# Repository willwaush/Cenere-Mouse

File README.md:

# 🖱️ Cenere Mouse (Open Source Tri-Mode Connectivity)

---

## 🔎 Project Overview

This project is an **open-source tri-mode connectivity gaming mouse**, designed around the **Nordic nRF52840** SoC.  
It supports three connectivity modes:

- **USB HID**  
- **Bluetooth Low Energy (BLE)**  
- **Nordic 2.4 GHz Wireless protocol**  

### ✨ Key Features
- Custom **monopole 2.4 GHz PCB antenna** optimized for the nRF52840  
- **PixArt PAW3395 optical sensor** for high-precision tracking  
- **Battery charging circuit** to support Bluetooth and Wireless power  
- **DC/DC Supply** to achieve maximum efficiency, low energy consumption
- **Addressable RGB LEDs** to optionally enable some aestethic glowing effect
- Fully open-source hardware and firmware*

---

## 📐 PCB Layer Previews

The design is a **4-layer PCB**, manufactured by **JLCPCB**, chosen for their reliable stackup and cost-effective prototyping services.  

---

## 🏗️ PCB Stackup (JLCPCB)

The board will be fabricated at **JLCPCB** with the following stackup:

- **Top Layer (Copper, 35 µm)** – signal + components  
- **Prepreg (0.2104 mm, Dk ≈ 4.4)** – dielectric (7628*1) 
- **Mid Layer 1 (Copper, 152 µm)** – ground/pwr
- **Core (1.065 mm, Dk ≈ 4.6)** – dielectric (FR4)
- **Mid Layer 2 (Copper, 152 µm)** – ground/pwr
- **Prepreg (0.2104 mm, Dk ≈ 4.4)** – dielectric (7628*1) 
- **Bottom Layer (Copper, 35 µm)** – signal + components

This configuration provides an easy to work with controlled impedance environment for the **high speed signals** as well as the **RF Section**.

---

## 🚀 Goals

- Provide a **fully open-source reference design** for hobbyists, makers, and researchers  
- Explore advanced **antenna design** on low-cost PCB fabrication  
- Enable experimentation with **custom gaming peripherals**  

---

## 📂 Repository Structure

/Kicad Files        → KiCad design files
/Electronics Docs   → Documentation, layer renders, diagrams

Work in progress..

---

## 📜 License

This project uses a **dual-license** model:

- **Software (Code)** → [GNU GPL v3.0](LICENSES/GPL-3.0.txt) with a **Non-Commercial Use Exception**  
  - You may use, modify, and redistribute the source code for **personal, educational, or research** purposes.  
  - **Commercial use is prohibited** without prior written permission.  
  - Attribution is required.

- **Hardware (Schematics, PCB Layouts, Documentation)** → [CC BY-NC 4.0](LICENSES/CC-BY-NC-4.0.txt)  
  - You may copy, redistribute, remix, and adapt the hardware files.  
  - **Commercial use is prohibited.**  
  - Attribution is required.

### Attribution Requirement

If you use this project (code or hardware) in your own work, you must credit:

**© [Your Name or Handle] – [Year]**  
Repo: [GitHub Repository URL]

Example attribution:  
> “Based on the open-source design/code by [Your Name], available at [GitHub Repo URL].”

### Commercial Use

For commercial licensing, please contact the author.

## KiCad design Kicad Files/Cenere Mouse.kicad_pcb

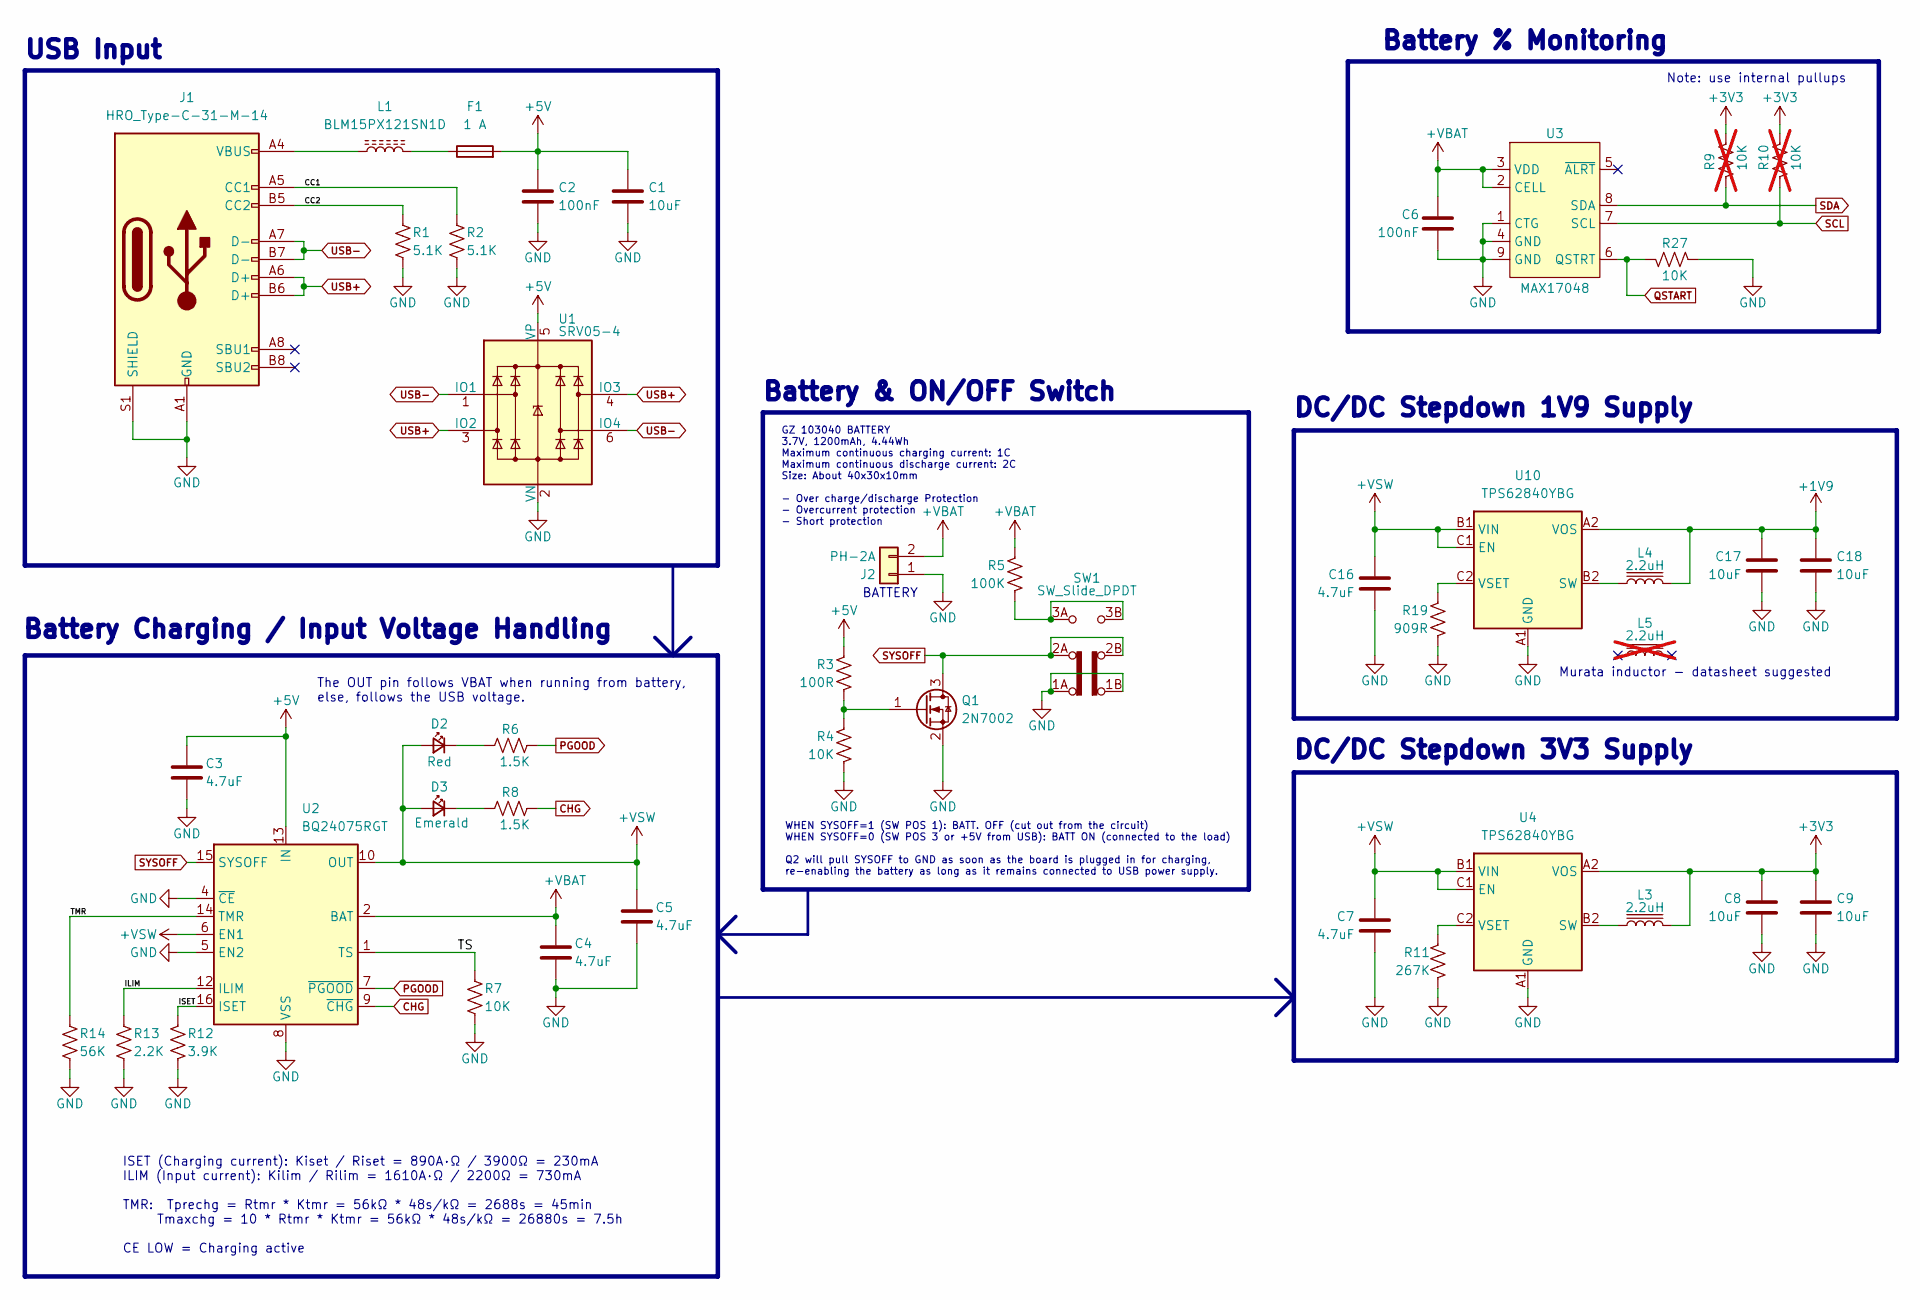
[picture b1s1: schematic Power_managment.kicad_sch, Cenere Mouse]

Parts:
C1, C9, C18: 10uF; C_0805_2012Metric; Part Number CL21B106KOQNNNE; JLCPCB PN C95841
C2: 100nF; C_0805_2012Metric; Part Number CC0805KRX7R9BB104; JLCPCB PN C49678
C3: 4.7uF; C_1206_3216Metric; Part Number 1206B475K500NT; JLCPCB PN C29823
C4, C5: 4.7uF; C_0805_2012Metric; Part Number CGA0805X7R475K350MT; JLCPCB PN C6119943
C6: 100nF; C_0402_1005Metric; Part Number CL05B104KB54PNC; JLCPCB PN C307331
C7, C16: 4.7uF; C_0402_1005Metric; Part Number CL05A475MP5NRNC; JLCPCB PN C23733
C8, C17: 10uF; C_0402_1005Metric; Part Number CL05A106MQ5NUNC; JLCPCB PN C15525
D2: Red; LED_0603_1608Metric; Part Number KT-0603R; JLCPCB PN C2286
D3: Emerald; LED_0603_1608Metric; Part Number APTD1608CGCK; JLCPCB PN C5121471
F1: 1 A; Fuse_0603_1608Metric; Part Number 0467001.NRHF; JLCPCB PN C151139
J1: HRO_Type-C-31-M-14; USB_C_Receptacle_HRO_TYPE-C-31-M-14; Part Number TYPE-C-31-M-14; JLCPCB PN C223907
J2: PH-2A; JST_PH_B2B-PH-K_1x02_P2.00mm_Vertical; Part Number PH-2A; JLCPCB PN C2319
L1: BLM15PX121SN1D; L_0402_1005Metric; Part Number BLM15PX121SN1D; JLCPCB PN C88970
L3, L4: 2.2uH; L_1008_2520Metric; Part Number FTC252012S2R2MBCA; JLCPCB PN C5832372
L5: 2.2uH; L_Murata_DFE201610P; Part Number DFE201612E-2R2M=P2; JLCPCB PN C337893; not fitted
Q1: 2N7002; SOT-23; Part Number 2N7002; JLCPCB PN C8545
R1, R2: 5.1K; R_0603_1608Metric; Part Number 0603WAF5101T5E; JLCPCB PN C23186
R3: 100R; R_0603_1608Metric; Part Number 0603WAF1000T5E; JLCPCB PN C22775
R4, R27: 10K; R_0603_1608Metric; Part Number 0603WAF1002T5E; JLCPCB PN C25804
R5: 100K; R_0603_1608Metric; Part Number 0603WAF1003T5E; JLCPCB PN C25803
R6, R8: 1.5K; R_0603_1608Metric; Part Number 0603WAF1501T5E; JLCPCB PN C22843
R7: 10K; R_0805_2012Metric; Part Number 0805W8F1002T5E; JLCPCB PN C17414
R9, R10: 10K; R_0603_1608Metric; Part Number 0603WAF1002T5E; JLCPCB PN C25804; not fitted
R11: 267K; R_0402_1005Metric; Part Number FRC0402F2673TS; JLCPCB PN C2998050
R12: 3.9K; R_0603_1608Metric; Part Number 0603WAF3901T5E; JLCPCB PN C23018
R13: 2.2K; R_0402_1005Metric; Part Number 0402WGF2201TCE; JLCPCB PN C25879
R14: 56K; R_0402_1005Metric; Part Number 0402WGF5602TCE; JLCPCB PN C25796
R19: 909R; R_0603_1608Metric; Part Number RC0603DR-07909RL; JLCPCB PN C471842
SW1: SW_Slide_DPDT; SLIDE SMD DPDT
U1: SRV05-4; SOT-23-6; Part Number SRV05-4; JLCPCB PN C2836319
U2: BQ24075RGT; VQFN-16-1EP_3x3mm_P0.5mm_EP1.6x1.6mm_ThermalVias; Part Number BQ24075RGTR; JLCPCB PN C15464
U3: MAX17048; TDFN-8-EP_2x2mm_EP_0.8x1.38mm; Part Number MAX17048G+T10; JLCPCB PN C2682616
U4, U10: TPS62840YBG; Texas_DSBGA-6_0.76x1.16mm_Layout2x3_P0.4mm; Part Number TPS62840YBGR; JLCPCB PN C2071139

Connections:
+1V9: C17.1, C18.1, L4.2, U10.A2 (VOS); also elsewhere on the board
+3V3: C8.1, C9.1, L3.2, R9.2, R10.2, U4.A2 (VOS); also elsewhere on the board
+5V: C1.1, C2.1, C3.1, F1.2, R3.1, U1.5 (VP), U2.13 (IN); also elsewhere on the board
+VBAT: C4.1, C6.1, J2.2, R5.1, U2.2 (BAT), U2.3 (BAT), U3.2 (CELL), U3.3 (VDD)
+VSW: C5.1, C7.1, C16.1, D2.2 (A), D3.2 (A), U2.6 (EN1), U2.10 (OUT), U2.11 (OUT), U4.B1 (VIN), U4.C1 (EN), U10.B1 (VIN), U10.C1 (EN); also elsewhere on the board
/Power_managment/CC1: J1.A5 (CC1), R2.1
/Power_managment/CC2: J1.B5 (CC2), R1.1
/Power_managment/ILIM: R13.1, U2.12 (ILIM)
/Power_managment/ISET: R12.1, U2.16 (ISET)
/Power_managment/TMR: R14.1, U2.14 (TMR)
/Power_managment/TS: R7.1, U2.1 (TS)
CHG: R8.2, U2.9 (~CHG)
GND: C1.2, C2.2, C3.2, C4.2, C5.2, C6.2, C7.2, C8.2, C9.2, C16.2, C17.2, C18.2, J1.A1 (GND), J1.A12 (GND), J1.B1 (GND), J1.B12 (GND), J1.S1 (SHIELD), J2.1, Q1.2 (S), R1.2, R2.2, R4.2, R7.2, R11.2, R12.2, R13.2, R14.2, R19.2, R27.2, SW1.1A (NC), SW1.1B (NC), U1.2 (VN), U2.4 (~CE), U2.5 (EN2), U2.8 (VSS), U2.17 (VSS), U3.1 (CTG), U3.4 (GND), U3.9 (GND), U4.A1 (GND), U10.A1 (GND); also elsewhere on the board
unnamed: D2.1 (K), R6.1
unnamed: D3.1 (K), R8.1
unnamed: F1.1, L1.2
unnamed: J1.A4 (VBUS), J1.A9 (VBUS), J1.B4 (VBUS), J1.B9 (VBUS), L1.1
unnamed: Q1.1 (G), R3.2, R4.1
unnamed: R5.2, SW1.3A (NO), SW1.3B (NO)
unnamed: L3.1, U4.B2 (SW)
unnamed: R11.1, U4.C2 (VSET)
unnamed: L4.1, U10.B2 (SW)
unnamed: R19.1, U10.C2 (VSET)
PGOOD: R6.2, U2.7 (~PGOOD)
QSTART: R27.1, U3.6 (QSTRT); also elsewhere on the board
SCL: R10.1, U3.7 (SCL); also elsewhere on the board
SDA: R9.1, U3.8 (SDA); also elsewhere on the board
SYSOFF: Q1.3 (D), SW1.2A (COM), SW1.2B (COM), U2.15 (SYSOFF)
USB+: J1.A6 (D+), J1.B6 (D+), U1.3 (IO2), U1.4 (IO3); also elsewhere on the board
USB-: J1.A7 (D-), J1.B7 (D-), U1.1 (IO1), U1.6 (IO4); also elsewhere on the board

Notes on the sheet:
Note: use internal pullups
The OUT pin follows VBAT when running from battery, else, follows the USB voltage.
BATTERY
USB Input
GZ 103040 BATTERY 3.7V, 1200mAh, 4.44Wh Maximum continuous charging current: 1C Maximum continuous discharge current: 2C Size: About 40x30x10mm - Over charge/discharge Protection - Overcurrent protection - Short protection
DC/DC Stepdown 1V9 Supply
WHEN SYSOFF=1 (SW POS 1): BATT. OFF (cut out from the circuit) WHEN SYSOFF=0 (SW POS 3 or +5V from USB): BATT ON (connected to the load) Q2 will pull SYSOFF to GND as soon as the board is plugged in for charging, re-enabling the battery as long as it remains connected to USB power supply.
Battery % Monitoring
Murata inductor - datasheet suggested
Battery Charging / Input Voltage Handling
DC/DC Stepdown 3V3 Supply
Battery & ON/OFF Switch
ISET (Charging current): Kiset / Riset = 890A·Ω / 3900Ω = 230mA ILIM (Input current): Kilim / Rilim = 1610A·Ω / 2200Ω = 730mA TMR: Tprechg = Rtmr * Ktmr = 56kΩ * 48s/kΩ = 2688s = 45min Tmaxchg = 10 * Rtmr * Ktmr = 56kΩ * 48s/kΩ = 26880s = 7.5h CE LOW = Charging active

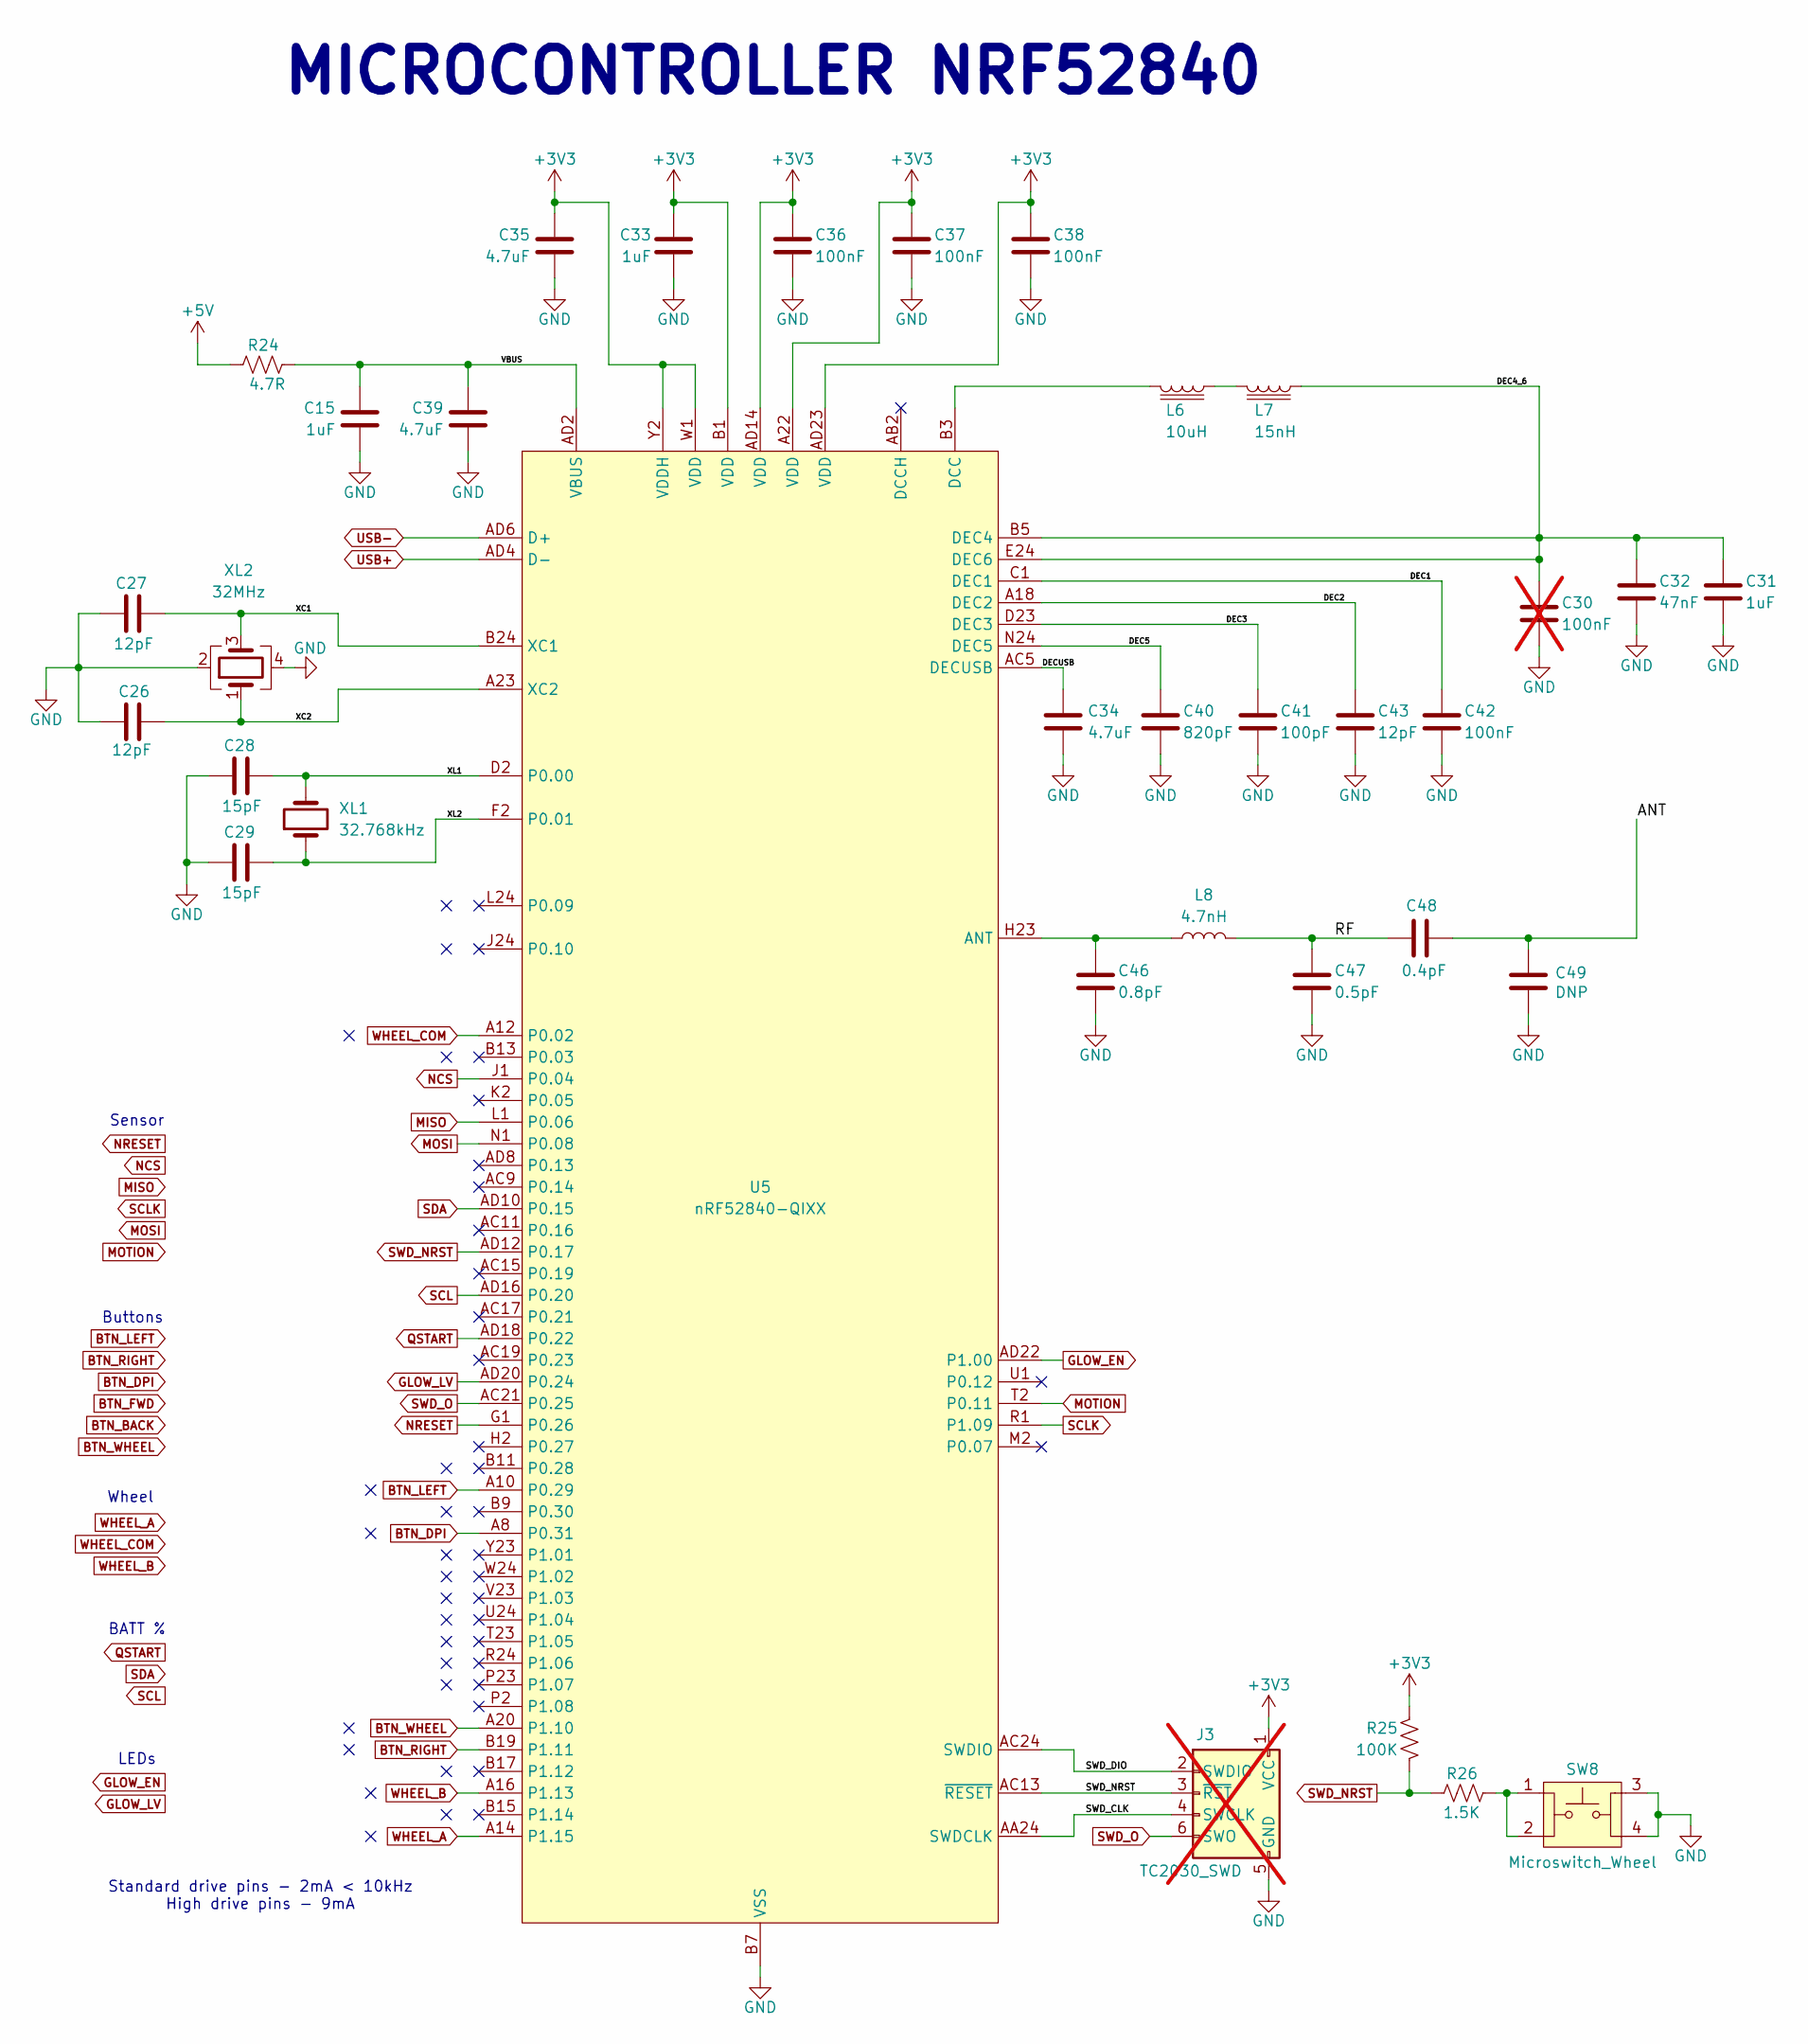
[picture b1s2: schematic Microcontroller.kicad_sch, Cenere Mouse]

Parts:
C15, C31, C33: 1uF; C_0402_1005Metric; Part Number CL05A105KA5NQNC; JLCPCB PN C52923
C26, C27, C43: 12pF; C_0402_1005Metric; Part Number 0402CG120J500NT; JLCPCB PN C1547
C28, C29: 15pF; C_0402_1005Metric; Part Number 0402CG150J500NT; JLCPCB PN C1548
C30: 100nF; C_0201_0603Metric; not fitted
C32: 47nF; C_0402_1005Metric; Part Number CC0402KRX7R9BB473; JLCPCB PN C272875
C34, C35, C39: 4.7uF; C_0402_1005Metric; Part Number CL05A475MP5NRNC; JLCPCB PN C23733
C36, C37, C38, C42: 100nF; C_0402_1005Metric; Part Number CL05B104KB54PNC; JLCPCB PN C307331
C40: 820pF; C_0402_1005Metric; Part Number CL05C821JB5NNNC; JLCPCB PN C307452
C41: 100pF; C_0402_1005Metric; Part Number 0402CG101J500NT; JLCPCB PN C1546
C46: 0.8pF; C_0402_1005Metric; Part Number GJM1555C1HR80WB01D; JLCPCB PN C88902
C47: 0.5pF; C_0402_1005Metric; Part Number GCM1555C1HR50WA16D; JLCPCB PN C2912277
C48: 0.4pF; Z0201 RF Antenna Path; Part Number GRM0335C1ER40WA01D; JLCPCB PN C710805
C49: DNP; Z0201 RF Antenna Path
J3: TC2030_SWD; CON_TC2030_outlined; not fitted
L6: 10uH; L_0603_1608Metric; Part Number LBMF1608T100M; JLCPCB PN C86752
L7: 15nH; L_0402_1005Metric; Part Number LQW15AN15NG80D; JLCPCB PN C668460
L8: 4.7nH; L_0402_1005Metric; Part Number LQG15HS4N7S02D; JLCPCB PN C86065
R24: 4.7R; R_0603_1608Metric; Part Number 0603WAF470KT5E; JLCPCB PN C23164
R25: 100K; R_0402_1005Metric; Part Number 0402WGF1003TCE; JLCPCB PN C25741
R26: 1.5K; R_0402_1005Metric; Part Number 0402WGF1501TCE; JLCPCB PN C25867
SW8: Microswitch_Wheel; KEY-SMD_4P-L4.2-W3.2-P2.20-LS4.6; Part Number SKRPACE010; JLCPCB PN C139797
U5: nRF52840-QIXX; Nordic_AQFN-73-1EP_7x7mm_P0.5mm; Part Number NRF52840-QIAA-R; JLCPCB PN C190794
XL1: 32.768kHz; Crystal_SMD_2012-2Pin_2.0x1.2mm; Part Number XKHEL89CGI-112YLC-32.768K; JLCPCB PN C7500573
XL2: 32MHz; Crystal_SMD_2016-4Pin_2.0x1.6mm; Part Number XL7EL89CKI-111YLC-32M; JLCPCB PN C2965582

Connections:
+3V3: C33.1, C35.1, C36.1, C37.1, C38.1, J3.1 (VCC), R25.1, U5.A22 (VDD), U5.AD14 (VDD), U5.AD23 (VDD), U5.B1 (VDD), U5.W1 (VDD), U5.Y2 (VDDH); also elsewhere on the board
+5V: R24.1; also elsewhere on the board
/Microcontroller/ANT: C48.2, C49.2
/Microcontroller/DEC1: C42.1, U5.C1 (DEC1)
/Microcontroller/DEC2: C43.2, U5.A18 (DEC2)
/Microcontroller/DEC3: C41.1, U5.D23 (DEC3)
/Microcontroller/DEC4_6: C30.1, C31.1, C32.1, L7.1, U5.B5 (DEC4), U5.E24 (DEC6)
/Microcontroller/DEC5: C40.1, U5.N24 (DEC5)
/Microcontroller/DECUSB: C34.1, U5.AC5 (DECUSB)
/Microcontroller/RF: C47.1, C48.1, L8.2
/Microcontroller/SWD_CLK: J3.4 (SWCLK), U5.AA24 (SWDCLK)
/Microcontroller/SWD_DIO: J3.2 (SWDIO), U5.AC24 (SWDIO)
/Microcontroller/VBUS: C15.1, C39.1, R24.2, U5.AD2 (VBUS)
/Microcontroller/XC1: C27.2, U5.B24 (XC1), XL2.3
/Microcontroller/XC2: C26.1, U5.A23 (XC2), XL2.1
/Microcontroller/XL1: C28.2, U5.D2 (P0.00), XL1.2
/Microcontroller/XL2: C29.2, U5.F2 (P0.01), XL1.1
BTN_DPI: U5.A8 (P0.31); also elsewhere on the board
BTN_LEFT: U5.A10 (P0.29); also elsewhere on the board
BTN_RIGHT: U5.B19 (P1.11); also elsewhere on the board
BTN_WHEEL: U5.A20 (P1.10); also elsewhere on the board
GLOW_EN: U5.AD22 (P1.00); also elsewhere on the board
GLOW_LV: U5.AD20 (P0.24); also elsewhere on the board
GND: C15.2, C26.2, C27.1, C28.1, C29.1, C30.2, C31.2, C32.2, C33.2, C34.2, C35.2, C36.2, C37.2, C38.2, C39.2, C40.2, C41.2, C42.2, C43.1, C46.2, C47.2, C49.1, J3.5 (GND), SW8.3, SW8.4, U5.B7 (VSS), U5.EP (VSS), U5.F23 (VSS_PA), XL2.2, XL2.4; also elsewhere on the board
MISO: U5.L1 (P0.06); also elsewhere on the board
MOSI: U5.N1 (P0.08); also elsewhere on the board
MOTION: U5.T2 (P0.11); also elsewhere on the board
NCS: U5.J1 (P0.04); also elsewhere on the board
NRESET: U5.G1 (P0.26); also elsewhere on the board
unnamed: L6.1, L7.2
unnamed: R26.2, SW8.1, SW8.2
unnamed: C46.1, L8.1, U5.H23 (ANT)
unnamed: L6.2, U5.B3 (DCC)
QSTART: U5.AD18 (P0.22); also elsewhere on the board
SCL: U5.AD16 (P0.20); also elsewhere on the board
SCLK: U5.R1 (P1.09); also elsewhere on the board
SDA: U5.AD10 (P0.15); also elsewhere on the board
SWD_NRST: J3.3 (~RST), R25.2, R26.1, U5.AC13 (~RESET), U5.AD12 (P0.17)
SWD_O: J3.6 (SWO), U5.AC21 (P0.25)
USB+: U5.AD4 (D-); also elsewhere on the board
USB-: U5.AD6 (D+); also elsewhere on the board
WHEEL_A: U5.A14 (P1.15); also elsewhere on the board
WHEEL_B: U5.A16 (P1.13); also elsewhere on the board
WHEEL_COM: U5.A12 (P0.02); also elsewhere on the board

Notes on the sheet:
Standard drive pins - 2mA < 10kHz High drive pins - 9mA
BATT %
Buttons
MICROCONTROLLER NRF52840
Sensor
Wheel
LEDs

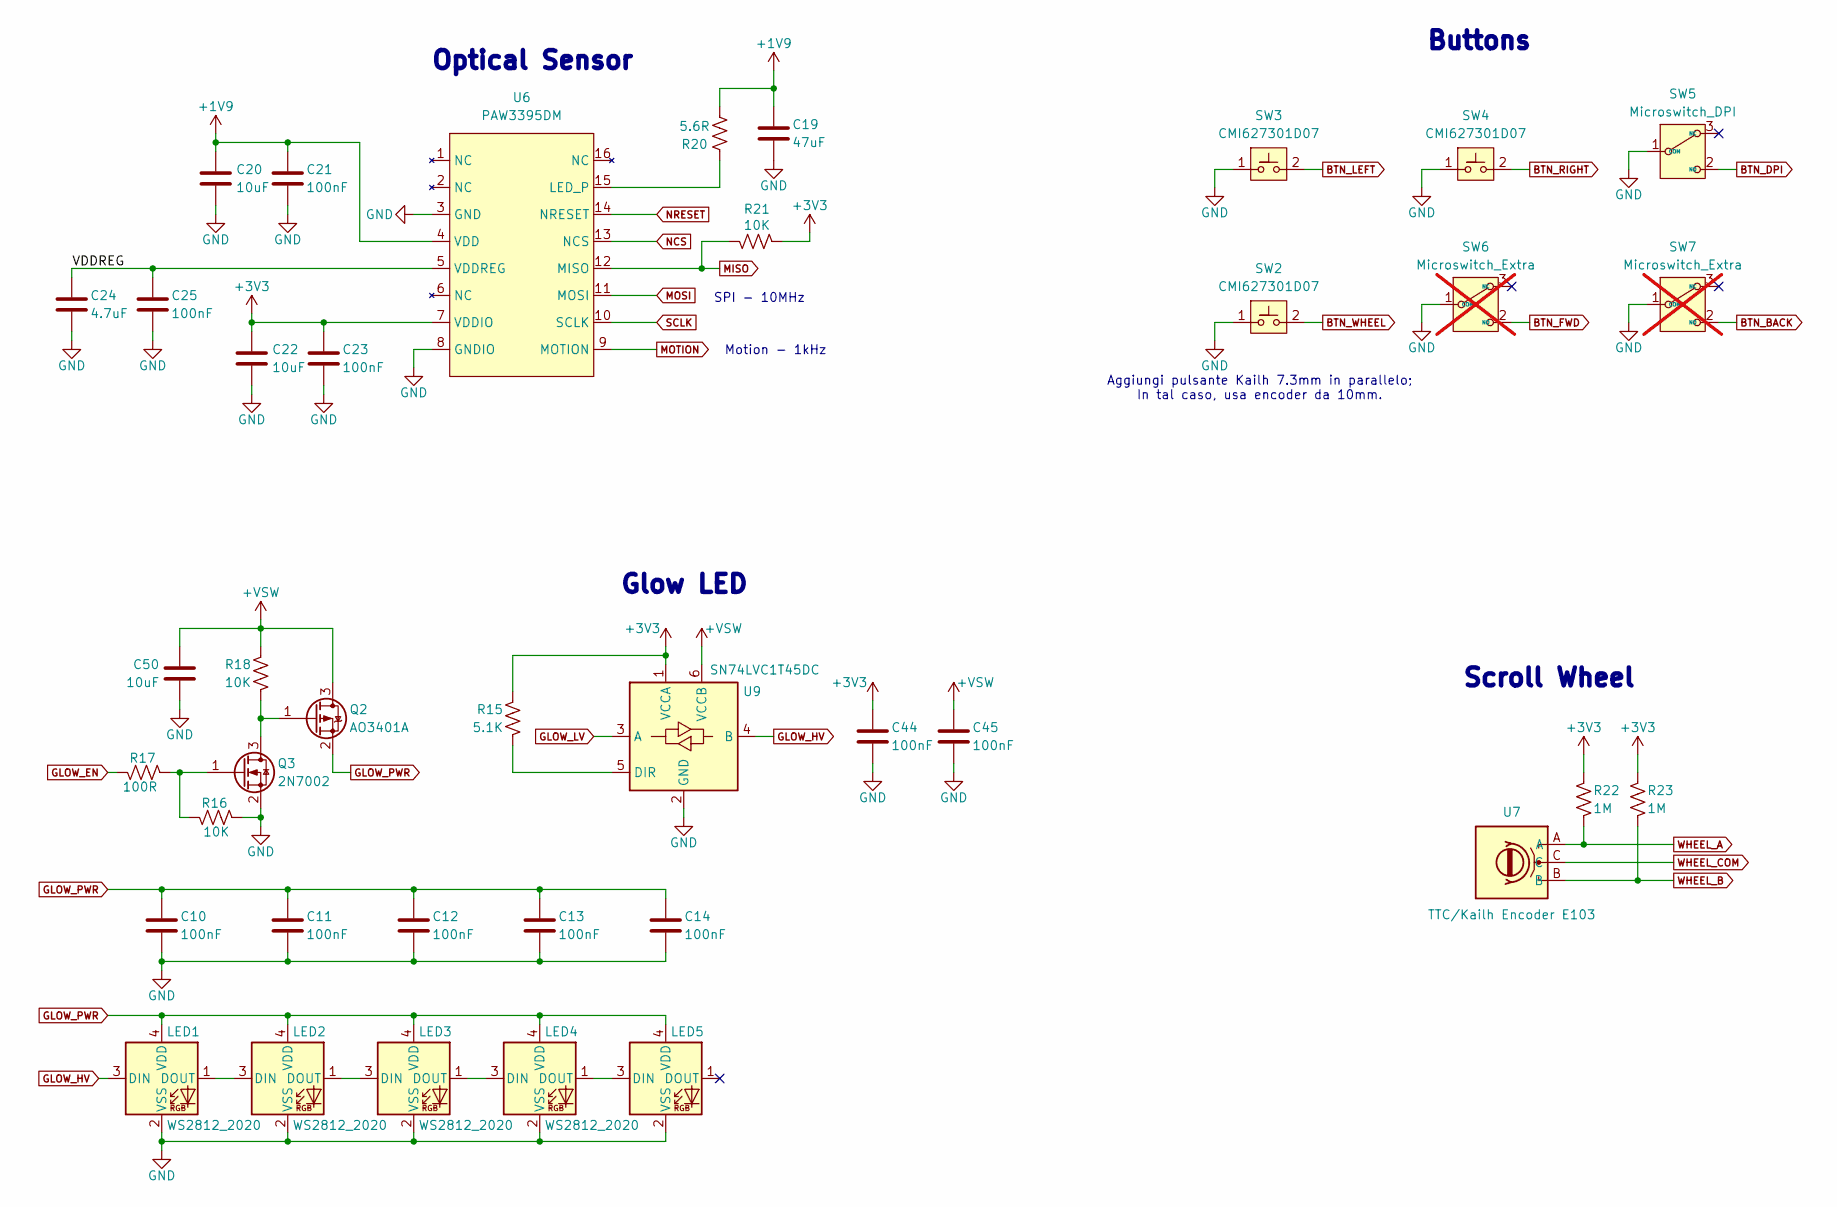
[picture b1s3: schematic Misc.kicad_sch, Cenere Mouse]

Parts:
C10, C11, C12, C13, C14, C21, C23, C25, C44, C45: 100nF; C_0402_1005Metric; Part Number CL05B104KB54PNC; JLCPCB PN C307331
C19: 47uF; C_1210_3225Metric; Part Number GRM32ER71A476KE15L; JLCPCB PN C84494
C20, C22, C50: 10uF; C_0805_2012Metric; Part Number CL21B106KOQNNNE; JLCPCB PN C95841
C24: 4.7uF; C_0805_2012Metric; Part Number CGA0805X7R475K350MT; JLCPCB PN C6119943
LED1, LED2, LED3, LED4, LED5: WS2812_2020; LED_WS2812_2020; Part Number WS2812B-2020; JLCPCB PN C965555
Q2: AO3401A; SOT-23; Part Number AO3401A; JLCPCB PN C347476
Q3: 2N7002; SOT-23; Part Number 2N7002; JLCPCB PN C8545
R15: 5.1K; R_0603_1608Metric; Part Number 0603WAF5101T5E; JLCPCB PN C23186
R16, R18, R21: 10K; R_0603_1608Metric; Part Number 0603WAF1002T5E; JLCPCB PN C25804
R17: 100R; R_0603_1608Metric; Part Number 0603WAF1000T5E; JLCPCB PN C22775
R20: 5.6R; R_0805_2012Metric; Part Number 0805W8F560KT5E; JLCPCB PN C17729
R22, R23: 1M; R_0603_1608Metric; Part Number 0603WAF1004T5E; JLCPCB PN C22935
SW2, SW3, SW4: CMI627301D07; SW_Tactile_SPST_ Kailh_6x6x7.3mm_Mute_Silent; Part Number CMI627301D07; JLCPCB PN C400268
SW5: Microswitch_DPI; SW_Tactile_SPDT_Omron_D2F; Part Number CMI126603D09; JLCPCB PN C400257
SW6, SW7: Microswitch_Extra; SW_Tactile_SPDT_Omron_D2F; not fitted
U6: PAW3395DM; PixArt_PDIP-16_10.9x16.2mm_P1.78mm; Part Number PAW3395
U7: TTC/Kailh Encoder E103; TTC E103 - Kailh Rotary Encoder
U9: SN74LVC1T45DC; SOT-363_SC-70-6; Part Number SN74LVC1T45DC; JLCPCB PN C9382

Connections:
+1V9: C19.1, C20.1, C21.1, R20.2, U6.4 (VDD); also elsewhere on the board
+3V3: C22.1, C23.1, C44.1, R15.1, R21.1, R22.1, R23.1, U6.7 (VDDIO), U9.1 (VCCA); also elsewhere on the board
+VSW: C45.1, C50.1, Q2.3 (D), R18.1, U9.6 (VCCB); also elsewhere on the board
/Misc/VDDREG: C24.1, C25.1, U6.5 (VDDREG)
BTN_DPI: SW5.2 (NO); also elsewhere on the board
BTN_LEFT: SW3.2; also elsewhere on the board
BTN_RIGHT: SW4.2; also elsewhere on the board
BTN_WHEEL: SW2.2; also elsewhere on the board
GLOW_EN: R17.1; also elsewhere on the board
GLOW_HV: LED1.3 (DIN), U9.4 (B)
GLOW_LV: U9.3 (A); also elsewhere on the board
GLOW_PWR: C10.1, C11.1, C12.1, C13.1, C14.1, LED1.4 (VDD), LED2.4 (VDD), LED3.4 (VDD), LED4.4 (VDD), LED5.4 (VDD), Q2.2 (S)
GND: C10.2, C11.2, C12.2, C13.2, C14.2, C19.2, C20.2, C21.2, C22.2, C23.2, C24.2, C25.2, C44.2, C45.2, C50.2, LED1.2 (VSS), LED2.2 (VSS), LED3.2 (VSS), LED4.2 (VSS), LED5.2 (VSS), Q3.2 (S), R16.2, SW2.1, SW3.1, SW4.1, SW5.1 (COM), SW6.1 (COM), SW7.1 (COM), U6.3 (GND), U6.8 (GNDIO), U9.2 (GND); also elsewhere on the board
MISO: R21.2, U6.12 (MISO); also elsewhere on the board
MOSI: U6.11 (MOSI); also elsewhere on the board
MOTION: U6.9 (MOTION); also elsewhere on the board
NCS: U6.13 (NCS); also elsewhere on the board
NRESET: U6.14 (NRESET); also elsewhere on the board
unnamed: LED1.1 (DOUT), LED2.3 (DIN)
unnamed: LED2.1 (DOUT), LED3.3 (DIN)
unnamed: LED3.1 (DOUT), LED4.3 (DIN)
unnamed: LED4.1 (DOUT), LED5.3 (DIN)
unnamed: Q2.1 (G), Q3.3 (D), R18.2
unnamed: Q3.1 (G), R16.1, R17.2
unnamed: R20.1, U6.15 (LED_P)
unnamed: R15.2, U9.5 (DIR)
SCLK: U6.10 (SCLK); also elsewhere on the board
WHEEL_A: R22.2, U7.A; also elsewhere on the board
WHEEL_B: R23.2, U7.B; also elsewhere on the board
WHEEL_COM: U7.C; also elsewhere on the board

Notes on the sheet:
SPI - 10MHz
Glow LED
Motion - 1kHz
Scroll Wheel
Optical Sensor
Buttons
Aggiungi pulsante Kailh 7.3mm in parallelo; In tal caso, usa encoder da 10mm.

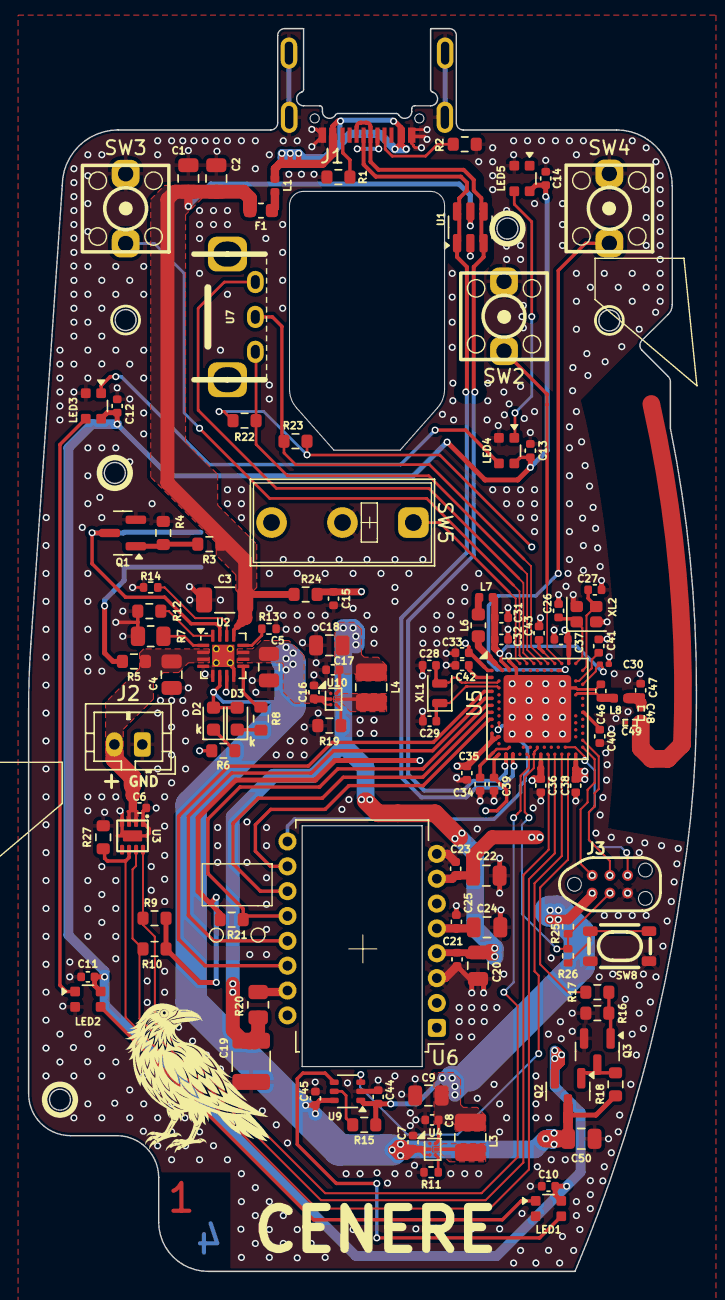
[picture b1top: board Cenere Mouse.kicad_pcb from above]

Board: 4 copper layers, 47.8 x 89.0 mm, 114 parts (1 on the bottom side), 77 nets.

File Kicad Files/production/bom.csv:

Designator,Footprint,Quantity,Value,LCSC Part #
"C1, C18, C20, C22, C50, C9",0805,6,10uF,C95841
"C10, C11, C12, C13, C14, C21, C23, C25, C36, C37, C38, C42, C44, C45, C6",0402,15,100nF,C307331
"C15, C31, C33",0402,3,1uF,C52923
"C16, C34, C35, C39, C7",0402,5,4.7uF,C23733
"C17, C8",0402,2,10uF,C15525
C19,1210,1,47uF,C84494
C2,0805,1,100nF,C49678
"C24, C4, C5",0805,3,4.7uF,C6119943
"C26, C27, C43",0402,3,12pF,C1547
"C28, C29",0402,2,15pF,C1548
C3,1206,1,4.7uF,C29823
C32,0402,1,47nF,C272875
C40,0402,1,820pF,C307452
C41,0402,1,100pF,C1546
C46,0402,1,0.8pF,C88902
C47,0402,1,0.5pF,C2912277
C48,Z0201 RF Antenna Path,1,0.4pF,C710805
D2,0603,1,Red,C2286
D3,0603,1,Emerald,C5121471
F1,0603,1,1 A,C151139
J1,USB_C_Receptacle_HRO_TYPE-C-31-M-14,1,HRO_Type-C-31-M-14,C223907
J2,JST_PH_B2B-PH-K_1x02_P2.00mm_Vertical,1,PH-2A,C2319
L1,0402,1,BLM15PX121SN1D,C88970
"L3, L4",1008,2,2.2uH,C5832372
L6,0603,1,10uH,C86752
L7,0402,1,15nH,C668460
L8,0402,1,4.7nH,C86065
"LED1, LED2, LED3, LED4, LED5",LED_WS2812_2020,5,WS2812_2020,C965555
"Q1, Q3",SOT-23,2,2N7002,C8545
Q2,SOT-23,1,AO3401A,C347476
"R1, R15, R2",0603,3,5.1K,C23186
R11,0402,1,267K,C2998050
R12,0603,1,3.9K,C23018
R13,0402,1,2.2K,C25879
R14,0402,1,56K,C25796
"R16, R18, R21, R27, R4",0603,5,10K,C25804
"R17, R3",0603,2,100R,C22775
R19,0603,1,909R,C471842
R20,0805,1,5.6R,C17729
"R22, R23",0603,2,1M,C22935
R24,0603,1,4.7R,C23164
R25,0402,1,100K,C25741
R26,0402,1,1.5K,C25867
R5,0603,1,100K,C25803
"R6, R8",0603,2,1.5K,C22843
R7,0805,1,10K,C17414
SW8,KEY-SMD_4P-L4.2-W3.2-P2.20-LS4.6,1,Microswitch_Wheel,C139797
U1,SOT-23-6,1,SRV05-4,C2836319
"U10, U4",Texas_DSBGA-6_0.76x1.16mm_Layout2x3_P0.4mm,2,TPS62840YBG,C2071139
U2,VQFN-16-1EP_3x3mm_P0.5mm_EP1.6x1.6mm_ThermalVias,1,BQ24075RGT,C15464
U3,TDFN-8-EP_2x2mm_EP_0.8x1.38mm,1,MAX17048,C2682616
U5,Nordic_AQFN-73-1EP_7x7mm_P0.5mm,1,nRF52840-QIXX,C190794
U6,PixArt_PDIP-16_10.9x16.2mm_P1.78mm,1,PAW3395DM,
U9,SOT-363_SC-70-6,1,SN74LVC1T45DC,C9382
XL1,Crystal_SMD_2012-2Pin_2.0x1.2mm,1,32.768kHz,C7500573
XL2,Crystal_SMD_2016-4Pin_2.0x1.6mm,1,32MHz,C2965582

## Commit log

2025-08-20 Initial commit
    Initial commit including:
    - Kicad design files
    - Electronics docs misc.
    - Licensing
    - Readme draft
2025-08-22 Minor improvements (detailed list attached)
    - Updated JST Connector to a more common PH 2.0mm one;
    - Added some helpful silkscreen;
    - Retouched some tracks;
    - Updated schematic symbols information to help “automatically” generate JLC BOM;
    - Adjusted Vias Annular ring sizes and clearances cleanup for JLC manufacturing;
    - Adjusted gitgnore to include .csv and .xml to show BOM files on Github;
